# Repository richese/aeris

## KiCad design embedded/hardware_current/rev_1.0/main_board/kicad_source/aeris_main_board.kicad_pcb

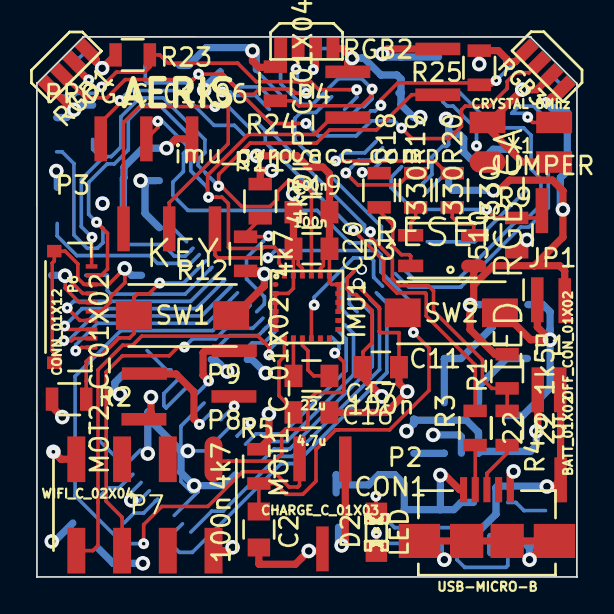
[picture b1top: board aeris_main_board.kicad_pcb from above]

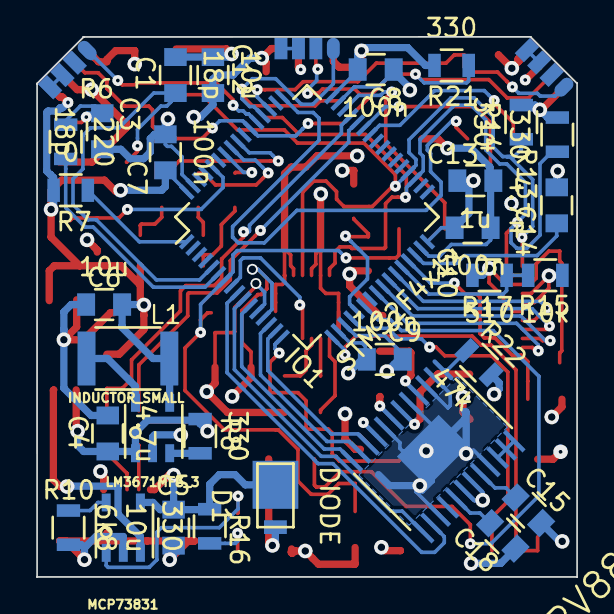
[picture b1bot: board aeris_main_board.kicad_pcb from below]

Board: 4 copper layers, 30.0 x 30.0 mm, 71 parts (31 on the bottom side), 69 nets.

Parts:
C1, C3: 18p; C_0805
C2, C7, C8, C9, C10, C11, C19, C20: 100n; C_0805
C4, C16: 4.7u; C_0805
C5, C6, C12: 10u; C_0805
C13: 1u; C_0805
C14: 4.7n; C_0805
C15: 10n; C_0805
C17: 22u; C_0805
C18: 2.2u; C_0805
CON1: USB-MICRO-B; Micro_USB_B
D1: DIODE; DO-220
D2: LED; LED-0805
D3: LED_RGB_CA; PLCC-4
IMU1: imu_gyro_acc_comp; LGA_24_max_pads
IO1: STM32F4x1x; LQFP-64_10x10mm_Pitch0.5mm
JP1: JUMPER; Header_2x1way_1_27mm
L1: INDUCTOR_SMALL; C_1812
P1: BATT_01X02; Header_2x1way_1_27mm
P2: CHARGE_C_01X03; Header_3x1way_1_27mm
P3: PROG_C_01X06; Header_6x1way_1_27_mm
P4: DISP_C_01X04; Header_4x1way_1_27_mm
P5: OFF_CON_01X02; Header_2x1way_1_27mm
P6: CONN_01X12; FFC_10way
P7: WIFI_C_02X04; PIN_2x4way_SMD_2_54
P8: MOT1_C_01X02; Header_2x1way_1_27mm
P9: MOT2_C_01X02; Header_2x1way_1_27mm
R1: 1k5; R_0805
R2, R5, R11, R12: 4k7; R_0805
R3, R4: 22; R_0805
R6: 220; R_0805
R7: 0; R_0805
R8, R13, R14, R16, R18, R19, R20, R21, R23, R24, R25: 330; R_0805
R9, R17: 510; R_0805
R10: 6k8; R_0805
R15: 10k; R_0805
R22: 47k; R_0805
RGB1, RGB2, RGB3: APDS_9950; RGB_LED_EDGE
SW1: KEY; DTSM-32S-B
SW2: RESET; DTSM-32S-B
U1: LM3671MF3_3; TSOT-23-5
U2: MCP73831; TSOT-23-5
U3: DRV8834; HTSSOP-24
X1: CRYSTAL 8Mhz; 5x3.2_CRYSTAL

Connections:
+3.3V: C6.1, C7.1, C8.1, C9.1, C10.1, C11.1, C12.1, C13.1, C19.1, C20.1, D3.CA, IMU1.15, IMU1.16, IMU1.17, IMU1.18, IMU1.19, IMU1.20, IO1.13, IO1.19, IO1.32, IO1.48, IO1.64, JP1.1, L1.2, P4.2, P6.4, P6.5, P7.2, R1.2, R2.1, R5.1, R7.2, R13.1, R14.1, R15.2, R21.2, R23.1, R24.1, R25.1, RGB1.5, RGB1.8, RGB2.5, RGB2.8, RGB3.5, RGB3.8, U1.4
+5V: C5.1, CON1.1, D1.2, R16.1, U2.4
+BATT: C4.1, C15.2, P5.2, R8.2, R11.2, R22.2, U1.1, U3.18, U3.19
//NS: IO1.24, P6.10
/A_PHASE: IO1.10, U3.13
/A_PWM: IO1.15, U3.10
/BAT_DIR: P1.2, P5.1, U2.3
/BOOT0: IO1.60, JP1.2, R9.1
/BOOT1: IO1.28, R15.1, R17.2
/B_PHASE: IO1.11, U3.12
/B_PWM: IO1.14, U3.11
/CHARG_ADC: IO1.22, P2.1
/KEY: IO1.29, R2.2, SW1.1
/M1: IO1.9, U3.14
/MISO: IO1.26, P6.8
/MOSI: IO1.27, P6.7
/Mystery_gyro_data_enable: IMU1.10, IO1.8
/RESET: C2.1, IO1.7, P3.1, R5.2, SW2.1
/RGB_B: IO1.58, R18.2
/RGB_G: IO1.57, R19.2
/RGB_R: IO1.56, R20.2
/SCK: IO1.25, P6.9
/SCL: IMU1.21, IO1.36, P4.3, P6.1, R14.2
/SCL_RGB: IO1.54, R21.1, RGB1.7, RGB2.7, RGB3.7
/SDA: IMU1.24, IO1.35, P4.4, P6.2, R13.2
/SDA_S1: IO1.51, R23.2, RGB1.1
/SDA_S2: IO1.52, R24.2, RGB2.1
/SDA_S3: IO1.53, R25.2, RGB3.1
/SWCLK: IO1.49, P3.4
/SWDIO: IO1.46, P3.3
/UART2_RX: IO1.17, P7.8
/UART2_TX: IO1.16, P7.1
/UART_RX: IO1.43, P3.5
/UART_TX: IO1.42, P3.6
/USB_DM: IO1.44, R3.2
/USB_DP: IO1.45, R1.1, R4.2
/VBAT_ADC: IO1.21, R11.1, R12.2
/VCAP1: C14.2, IO1.30
/WIFI_EN: IO1.20, P7.6
GND: C1.2, C2.2, C3.2, C4.2, C5.2, C6.2, C7.2, C8.2, C9.2, C10.2, C11.2, C12.2, C13.2, C14.1, C16.2, C18.1, C19.2, C20.2, CON1.5, CON1.6, CON1.7, CON1.8, CON1.9, IMU1.2, IMU1.3, IMU1.4, IMU1.5, IMU1.6, IMU1.22, IMU1.23, IO1.12, IO1.18, IO1.31, IO1.47, IO1.63, P1.1, P2.2, P3.2, P4.1, P6.3, P6.6, P6.11, P6.12, P7.7, R9.2, R10.1, R12.1, R17.1, RGB1.6, RGB2.6, RGB3.6, SW1.2, SW2.2, U1.2, U2.2, U3.2, U3.3, U3.5, U3.8, U3.15, U3.21, U3.PAD, X1.2, X1.4
unnamed: C1.1, IO1.5, X1.1
unnamed: C3.1, R6.2, X1.3
unnamed: C15.1, U3.17
unnamed: C16.1, IMU1.7
unnamed: C17.1, IMU1.8
unnamed: C17.2, IMU1.9
unnamed: C18.2, U3.20
unnamed: CON1.2, R3.1
unnamed: CON1.3, R4.1
unnamed: D1.1, P2.3
unnamed: D2.1, R16.2
unnamed: D2.2, U2.1
unnamed: D3.BC, R18.1
unnamed: D3.GC, R19.1
unnamed: D3.RC, R20.1
unnamed: IO1.1, R7.1
unnamed: IO1.6, R6.1
unnamed: L1.1, U1.5
unnamed: P8.1, U3.9
unnamed: P8.2, U3.7
unnamed: P9.1, U3.4
unnamed: P9.2, U3.6
unnamed: R8.1, U1.3
unnamed: R10.2, U2.5
unnamed: R22.1, U3.1
unnamed: RGB1.3, RGB1.4
unnamed: RGB2.3, RGB2.4
unnamed: RGB3.3, RGB3.4
unnamed: U3.22, U3.23, U3.24

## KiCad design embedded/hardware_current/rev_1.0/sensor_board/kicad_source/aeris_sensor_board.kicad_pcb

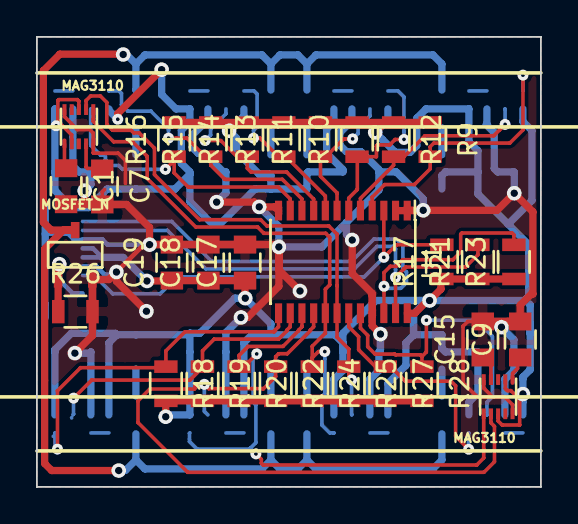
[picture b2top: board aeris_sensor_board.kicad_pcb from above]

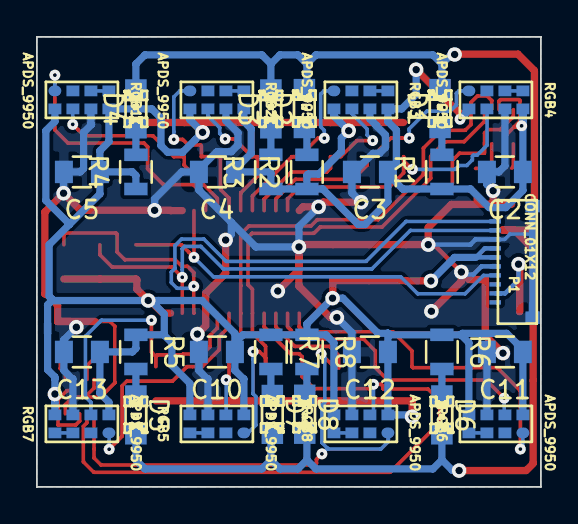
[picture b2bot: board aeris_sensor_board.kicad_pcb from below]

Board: 2 copper layers, 28.0 x 25.0 mm, 64 parts (33 on the bottom side), 43 nets.

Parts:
C1, C2, C3, C4, C5, C7, C9, C11, C12, C13, C15, C19: 100n; C_0805
C10: 100nv; C_0805
C17, C18: 1u; C_0805
D1, D2, D3, D4, D5, D6, D7, D8: LED; LED-0805
P1: CONN_01X12; FFC_10way
Q1: MOSFET_N; SOT-23
R1, R2, R3, R4, R5, R6, R7, R8, R9, R10, R11, R12, R13, R14, R15, R16, R17, R18, R19, R20, R21, R22, R23, R24, R25, R27, R28: 330; R_0805
R26: 4k7; R_0805
RGB1, RGB2, RGB3, RGB4, RGB5, RGB6, RGB7, RGB8: APDS_9950; RGB_LED
SENZ1, SENZ2: MAG3110; 2154-02
U1: PCA9548A; TSSOP-24_4.4x7.8mm_Pitch0.65mm

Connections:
+3.3V: C2.1, C3.1, C4.1, C5.1, C10.1, C11.1, C12.1, C13.1, C17.1, C18.1, C19.1, P1.6, P1.7, R1.1, R2.1, R3.1, R4.1, R5.1, R6.1, R7.1, R8.1, R9.1, R10.2, R11.2, R12.1, R13.2, R14.2, R15.2, R16.2, R17.1, R18.2, R19.2, R20.2, R21.1, R22.2, R23.1, R24.2, R25.2, R27.2, R28.2, RGB1.5, RGB1.8, RGB2.5, RGB2.8, RGB3.5, RGB3.8, RGB4.5, RGB4.8, RGB5.5, RGB5.8, RGB6.5, RGB6.8, RGB7.5, RGB7.8, RGB8.5, RGB8.8, SENZ1.2, SENZ1.8, SENZ2.2, SENZ2.8, U1.24
GND: C1.2, C2.2, C3.2, C4.2, C5.2, C7.2, C9.2, C10.2, C11.2, C12.2, C13.2, C15.2, C17.2, C18.2, C19.2, P1.5, P1.8, P1.11, P1.12, Q1.S, R26.2, RGB1.6, RGB2.6, RGB3.6, RGB4.6, RGB5.6, RGB6.6, RGB7.6, RGB8.6, SENZ1.5, SENZ1.10, SENZ2.5, SENZ2.10, U1.1, U1.2, U1.12, U1.21
IR: D1.2, D2.2, D3.2, D4.2, D5.2, D6.2, D7.2, D8.2, Q1.D
IR_CONTROLL: P1.2, Q1.G, R26.1
unnamed: C1.1, SENZ1.1
unnamed: C7.1, SENZ1.4
unnamed: C9.1, SENZ2.1
unnamed: C15.1, SENZ2.4
unnamed: D1.1, R1.2
unnamed: D2.1, R2.2
unnamed: D3.1, R3.2
unnamed: D4.1, R4.2
unnamed: D5.1, R5.2
unnamed: D6.1, R6.2
unnamed: D7.1, R7.2
unnamed: D8.1, R8.2
unnamed: RGB1.3, RGB1.4
unnamed: RGB2.3, RGB2.4
unnamed: RGB3.3, RGB3.4
unnamed: RGB4.3, RGB4.4
unnamed: RGB5.3, RGB5.4
unnamed: RGB6.3, RGB6.4
unnamed: RGB7.3, RGB7.4
unnamed: RGB8.3, RGB8.4
RESET: P1.4, R17.2, U1.3
SCL: P1.10, R23.2, U1.22
SC_A1: R25.1, RGB5.7, SENZ1.7, U1.18
SC_A2: R22.1, RGB8.7, SENZ2.7, U1.16
SC_B1: R19.1, RGB6.7, U1.14
SC_B2: R28.1, RGB7.7, U1.20
SC_F1: R12.2, RGB1.7, U1.5
SC_F2: R11.1, RGB2.7, U1.7
SC_F3: R14.1, RGB3.7, U1.9
SC_F4: R16.1, RGB4.7, U1.11
SDA: P1.9, R21.2, U1.23
SD_A1: R24.1, RGB5.1, SENZ1.6, U1.17
SD_A2: R20.1, RGB8.1, SENZ2.6, U1.15
SD_B1: R18.1, RGB6.1, U1.13
SD_B2: R27.1, RGB7.1, U1.19
SD_F1: R9.2, RGB1.1, U1.4
SD_F2: R10.1, RGB2.1, U1.6
SD_F3: R13.1, RGB3.1, U1.8
SD_F4: R15.1, RGB4.1, U1.10

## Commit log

2015-04-25 veriosn 1.0.2 added
2015-04-25 version 1.0.0 added
2015-04-25 common commit
2015-04-25 added robots suicide and gl_visualisation refresh group
2015-04-26 full pheromones support added and collective brain loading from files
2015-04-26 better pheromone spawning
2015-04-26 bin dirs added
2015-04-27 hardware release rev.1
2015-04-29 some work on Q learning
2015-04-30 work on wifi bootloader started
2015-05-01 work on wifi driver
2015-05-02 robot atomic packet container added, prepared for wifi communication
2015-05-02 clean up
2015-05-07 some work on ILC in ruby (in tmp)
2015-05-10 q-learning merging ability added, TODO: saving to file
2015-05-10 work on Qlearning saving
2015-05-10 brutal mess around Q learning cleaned up
2015-05-13 q leaning + agents works, TODO : Q matrix normalisation
2015-05-15 yeah, neural network on Q learning works!
2015-05-25 q learning tests
2015-06-01 some directories mess cleaned up
2015-06-15 kohonen + feed forward nn added as Q-table aproximation
2015-08-22 mess celaned up
2015-09-21 hal added
2015-09-23 line follower
2015-10-09 common
2016-02-08 new version
2016-02-11 cpu board
2016-02-19 aeris_2.0
2016-02-20 wifi driver added
2016-02-26 work on IMU
2016-02-26 rotation added
2016-02-28 sunday commit
2016-03-02 pictures + diagrams
2016-03-12 first version done
2016-03-13 we template
2016-03-15 visualsiation + line follower example
2016-03-15 picture
2016-03-29 Unified indent style of source files to tabs.
2016-04-06 color recognition
2016-04-06 micro bot added
2016-04-12 presentation
2016-05-03 Removed agent log files from git and added 'debug_log.txt', 'error_log.txt' to .gitignore. Rename 'run~' scripts to 'run'.
2016-05-03 Fix memory leak.
2016-05-03 Make it easier to pass optimization compiler flags.
2016-05-04 Bug fixes: - Join threads before calling delete on them. - Replace blocking call to `accept` in server loop with `select` with 1s timeout. Caused server to hang on shutdown. - Fix double free of `age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
2016-05-09 color_calib_bot base
